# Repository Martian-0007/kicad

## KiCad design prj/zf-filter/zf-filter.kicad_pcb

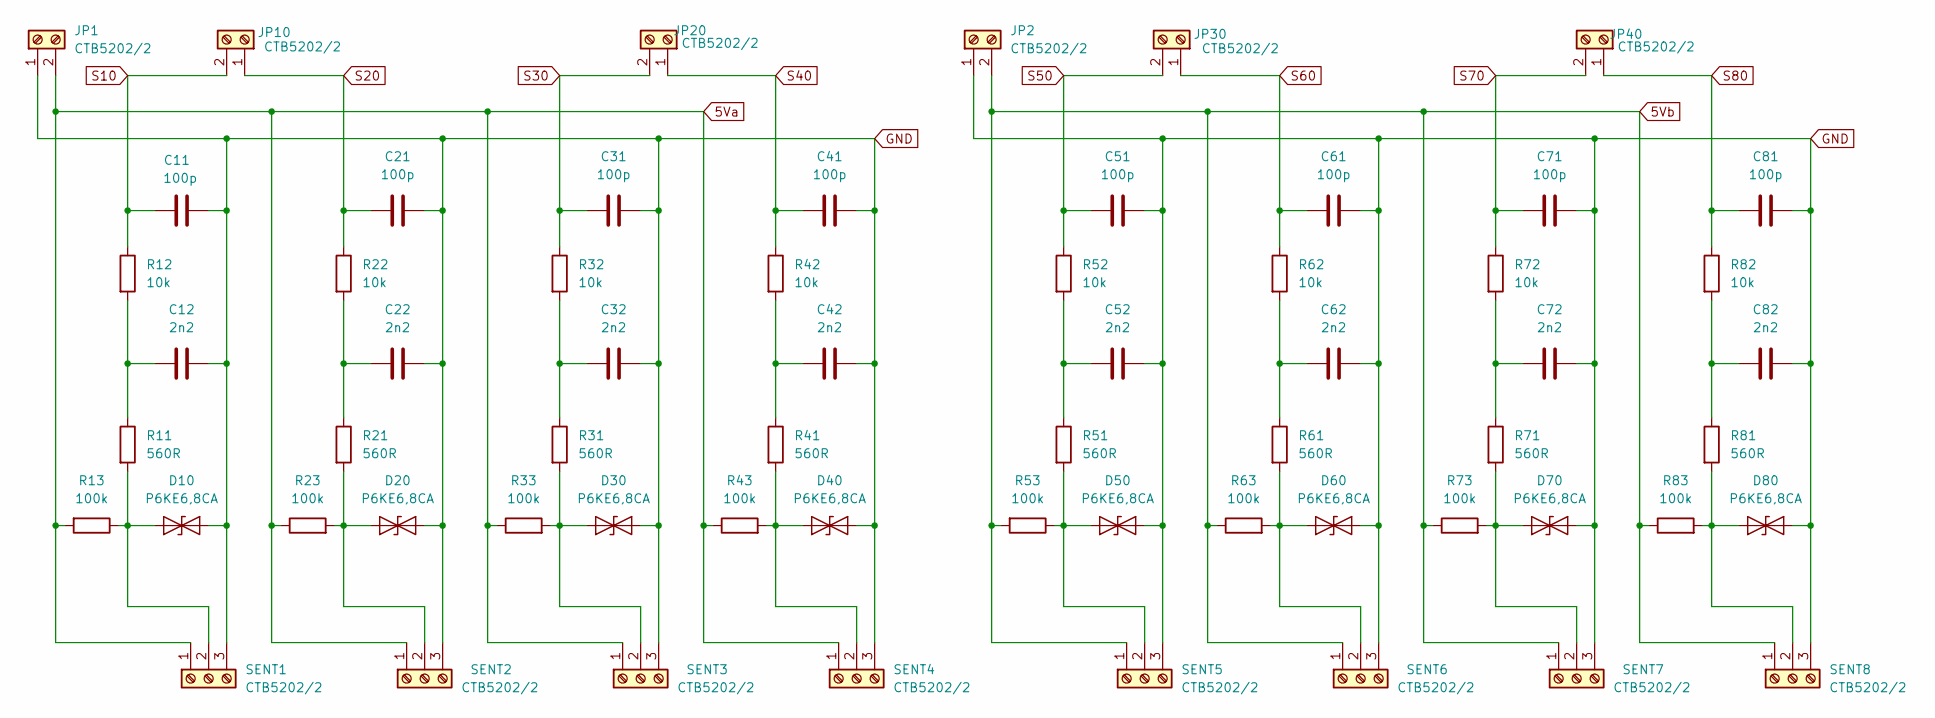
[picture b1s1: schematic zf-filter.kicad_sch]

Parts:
C11, C21, C31, C41, C51, C61, C71, C81: 100p; C_Disc_D6.0mm_W2.5mm_P5.00mm
C12, C22, C32, C42, C52, C62, C72, C82: 2n2; C_Rect_L7.2mm_W3.0mm_P5.00mm_FKS2_FKP2_MKS2_MKP2
D10, D20, D30, D40, D50, D60, D70, D80: P6KE6,8CA; D-THT-P6KE
JP1, JP2, JP10, JP20, JP30, JP40: CTB5202/2; TerminalBlock_RND_205-00001_1x02_P5.00mm_Horizontal
R11, R21, R31, R41, R51, R61, R71, R81: 560R; R_Axial_DIN0207_L6.3mm_D2.5mm_P10.16mm_Horizontal
R12, R22, R32, R42, R52, R62, R72, R82: 10k; R_Axial_DIN0207_L6.3mm_D2.5mm_P10.16mm_Horizontal
R13, R23, R33, R43, R53, R63, R73, R83: 100k; R_Axial_DIN0207_L6.3mm_D2.5mm_P10.16mm_Horizontal
SENT1, SENT2, SENT3, SENT4, SENT5, SENT6, SENT7, SENT8: CTB5202/2; TerminalBlock_RND_205-00002_1x03_P5.00mm_Horizontal

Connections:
5Va: JP1.2, R13.2, R23.1, R33.1, R43.1, SENT1.1, SENT2.1, SENT3.1, SENT4.1
5Vb: JP2.2, R53.2, R63.1, R73.1, R83.1, SENT5.1, SENT6.1, SENT7.1, SENT8.1
GND: C11.2, C12.2, C21.2, C22.2, C31.2, C32.2, C41.2, C42.2, C51.2, C52.2, C61.2, C62.2, C71.2, C72.2, C81.2, C82.2, D10.2 (A2), D20.2 (A2), D30.2 (A2), D40.2 (A2), D50.2 (A2), D60.2 (A2), D70.2 (A2), D80.2 (A2), JP1.1, JP2.1, SENT1.3, SENT2.3, SENT3.3, SENT4.3, SENT5.3, SENT6.3, SENT7.3, SENT8.3
unnamed: C12.1, R11.1, R12.2
unnamed: C22.1, R21.1, R22.2
unnamed: C32.1, R31.1, R32.2
unnamed: C42.1, R41.1, R42.2
unnamed: C52.1, R51.1, R52.2
unnamed: C62.1, R61.1, R62.2
unnamed: C72.1, R71.1, R72.2
unnamed: C82.1, R81.1, R82.2
unnamed: D10.1 (A1), R11.2, R13.1, SENT1.2
unnamed: D20.1 (A1), R21.2, R23.2, SENT2.2
unnamed: D30.1 (A1), R31.2, R33.2, SENT3.2
unnamed: D40.1 (A1), R41.2, R43.2, SENT4.2
unnamed: D50.1 (A1), R51.2, R53.1, SENT5.2
unnamed: D60.1 (A1), R61.2, R63.2, SENT6.2
unnamed: D70.1 (A1), R71.2, R73.2, SENT7.2
unnamed: D80.1 (A1), R81.2, R83.2, SENT8.2
S10: C11.1, JP10.2, R12.1
S20: C21.1, JP10.1, R22.1
S30: C31.1, JP20.2, R32.1
S40: C41.1, JP20.1, R42.1
S50: C51.1, JP30.2, R52.1
S60: C61.1, JP30.1, R62.1
S70: C71.1, JP40.2, R72.1
S80: C81.1, JP40.1, R82.1

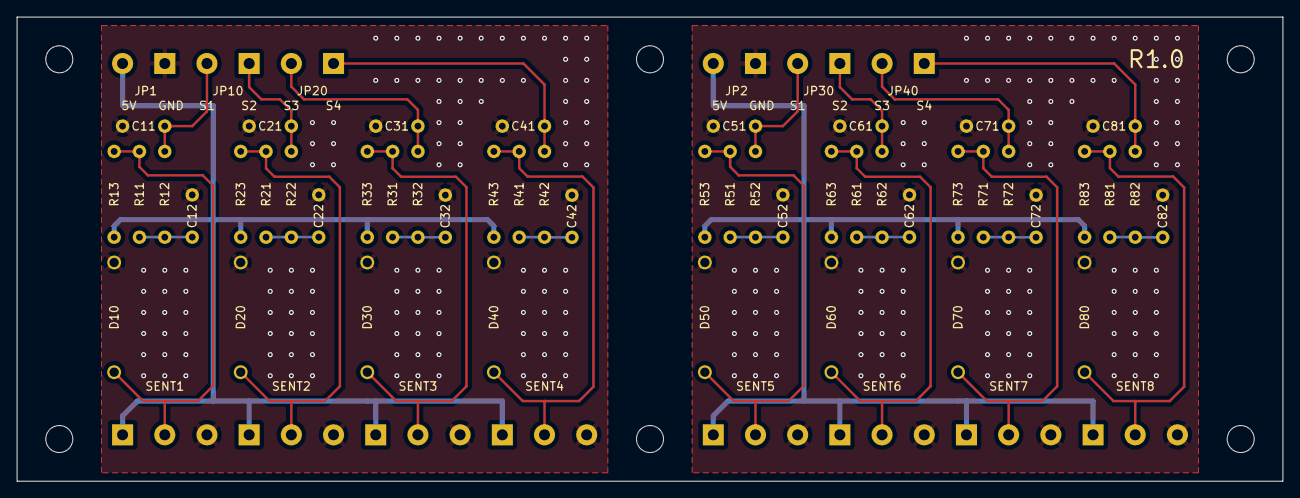
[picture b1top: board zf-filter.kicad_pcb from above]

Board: 2 copper layers, 150.0 x 55.0 mm, 62 parts (0 on the bottom side), 27 nets.

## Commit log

2024-02-28 Add KARA UAS ANT24A
2024-02-28 Removed .lck files
2024-03-06 Add converted and KiCad default libraries and reiew kara-uas-ant-24-a
2024-03-07 Add .gitignore
2024-03-11 Corrections to kara-uas-ant-24-a
2024-03-12 kara-uas-ant-24-a - center silkscreen frequency numbers
2024-03-12 kara-uas-ant-24-a - generate gerbers
2024-03-12 kara-uas-ant-24-a - regenerate gerbers
2024-03-13 Remove silkscreen from used footprints
2024-03-13 Add ZF-Filter
2024-03-20 move libraries 1/2
2024-03-20 move libraries 2/2
2024-03-20 zf-filter r1.0
2024-03-26 zf-filter r0.1
2024-03-26 Add SamacSys loader libs
2024-03-26 zf-filter r0.2
